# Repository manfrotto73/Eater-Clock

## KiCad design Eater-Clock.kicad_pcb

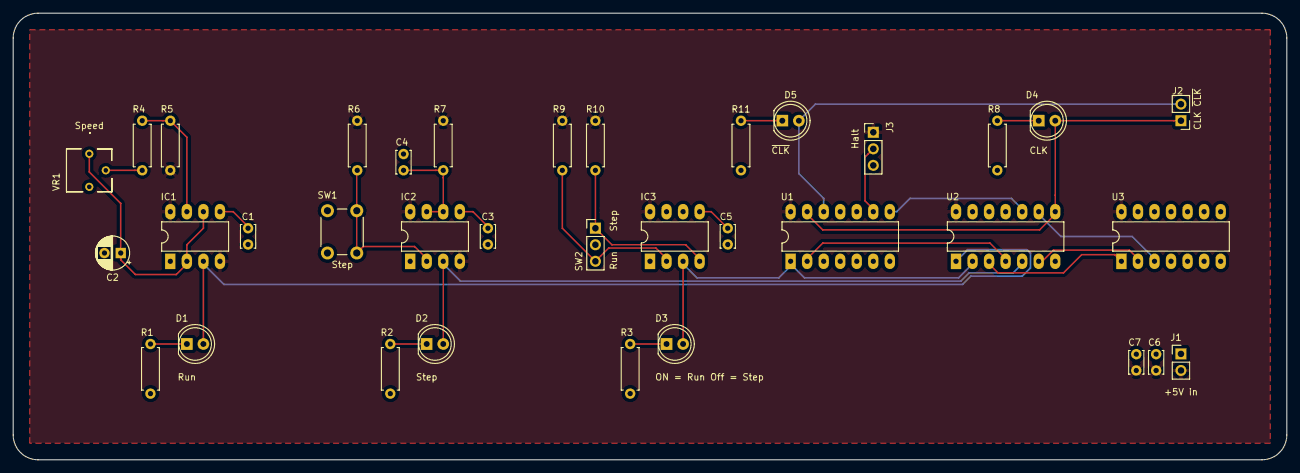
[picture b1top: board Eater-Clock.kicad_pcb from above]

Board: 2 copper layers, 195.6 x 68.6 mm, 35 parts (0 on the bottom side), 28 nets.

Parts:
C1, C3, C5: .01uF; C_Disc_D3.4mm_W2.1mm_P2.50mm
C2: 1uF; CP_Radial_D5.0mm_P2.50mm
C4, C6, C7: .1uF; C_Disc_D3.4mm_W2.1mm_P2.50mm
D1: Run; LED_D5.0mm
D2: Step; LED_D5.0mm
D3: ON = Run Off = Step; LED_D5.0mm
D4: CLK; LED_D5.0mm
D5: ~CLK; LED_D5.0mm
IC1, IC2, IC3: NE555; DIP-8_W7.62mm_LongPads
J1: +5V in; PinHeader_1x02_P2.54mm_Vertical
J2: CLK ~CLK; PinHeader_1x02_P2.54mm_Vertical
J3: Halt; PinHeader_1x03_P2.54mm_Vertical
R1, R2, R3, R8, R11: 240R; R_Axial_DIN0207_L6.3mm_D2.5mm_P7.62mm_Horizontal
R4, R5, R6: 1K; R_Axial_DIN0207_L6.3mm_D2.5mm_P7.62mm_Horizontal
R7: 1M; R_Axial_DIN0207_L6.3mm_D2.5mm_P7.62mm_Horizontal
R9, R10: 1k; R_Axial_DIN0207_L6.3mm_D2.5mm_P7.62mm_Horizontal
SW1: Step; SW_PUSH_6mm_H4.3mm
SW2: Run Step; PinHeader_1x03_P2.54mm_Vertical
U1: 74LS04; DIP-14_W7.62mm_LongPads
U2: 74LS08; DIP-14_W7.62mm_LongPads
U3: 74LS32; DIP-14_W7.62mm_LongPads
VR1: Speed; 3362P1105TLF

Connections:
+5V: C6.1, C7.1, IC1.4, IC1.8, IC2.4, IC2.8, IC3.8, J1.2, J3.1, R5.1, R6.1, R7.1, R9.1, R10.1, U1.14, U2.14, U3.14
CLK: D4.2, J2.1, U1.13, U2.8
GND: C1.2, C2.2, C3.2, C4.2, C5.2, C6.2, C7.2, IC1.1, IC2.1, IC3.1, IC3.6, J1.1, J3.3, R1.2, R2.2, R3.2, R8.2, R11.2, SW1.1, SW2.2, U1.7, U2.7, U3.7
INVCLK: D5.2, J2.2, U1.12
unnamed: C1.1, IC1.5
unnamed: C2.1, IC1.2, IC1.6, VR1.1
unnamed: C3.1, IC2.5
unnamed: C4.1, IC2.6, IC2.7, R7.2
unnamed: C5.1, IC3.5
unnamed: D1.1, R1.1
unnamed: D2.1, R2.1
unnamed: D3.1, R3.1
unnamed: D4.1, R8.1
unnamed: D5.1, R11.1
unnamed: IC1.7, R4.1, R5.2
unnamed: IC2.2, R6.2, SW1.2
unnamed: IC3.2, R9.2, SW2.3
unnamed: IC3.4, R10.2, SW2.1
unnamed: J3.2, U1.9
unnamed: R4.2, VR1.2
unnamed: U1.2, U2.4
unnamed: U1.8, U2.10
unnamed: U2.3, U3.1
unnamed: U2.6, U3.2
unnamed: U2.9, U3.3
U1-Q: D1.2, IC1.3, U2.1
U2-Q: D2.2, IC2.3, U2.5
U3-Q: D3.2, IC3.3, U1.1, U2.2
